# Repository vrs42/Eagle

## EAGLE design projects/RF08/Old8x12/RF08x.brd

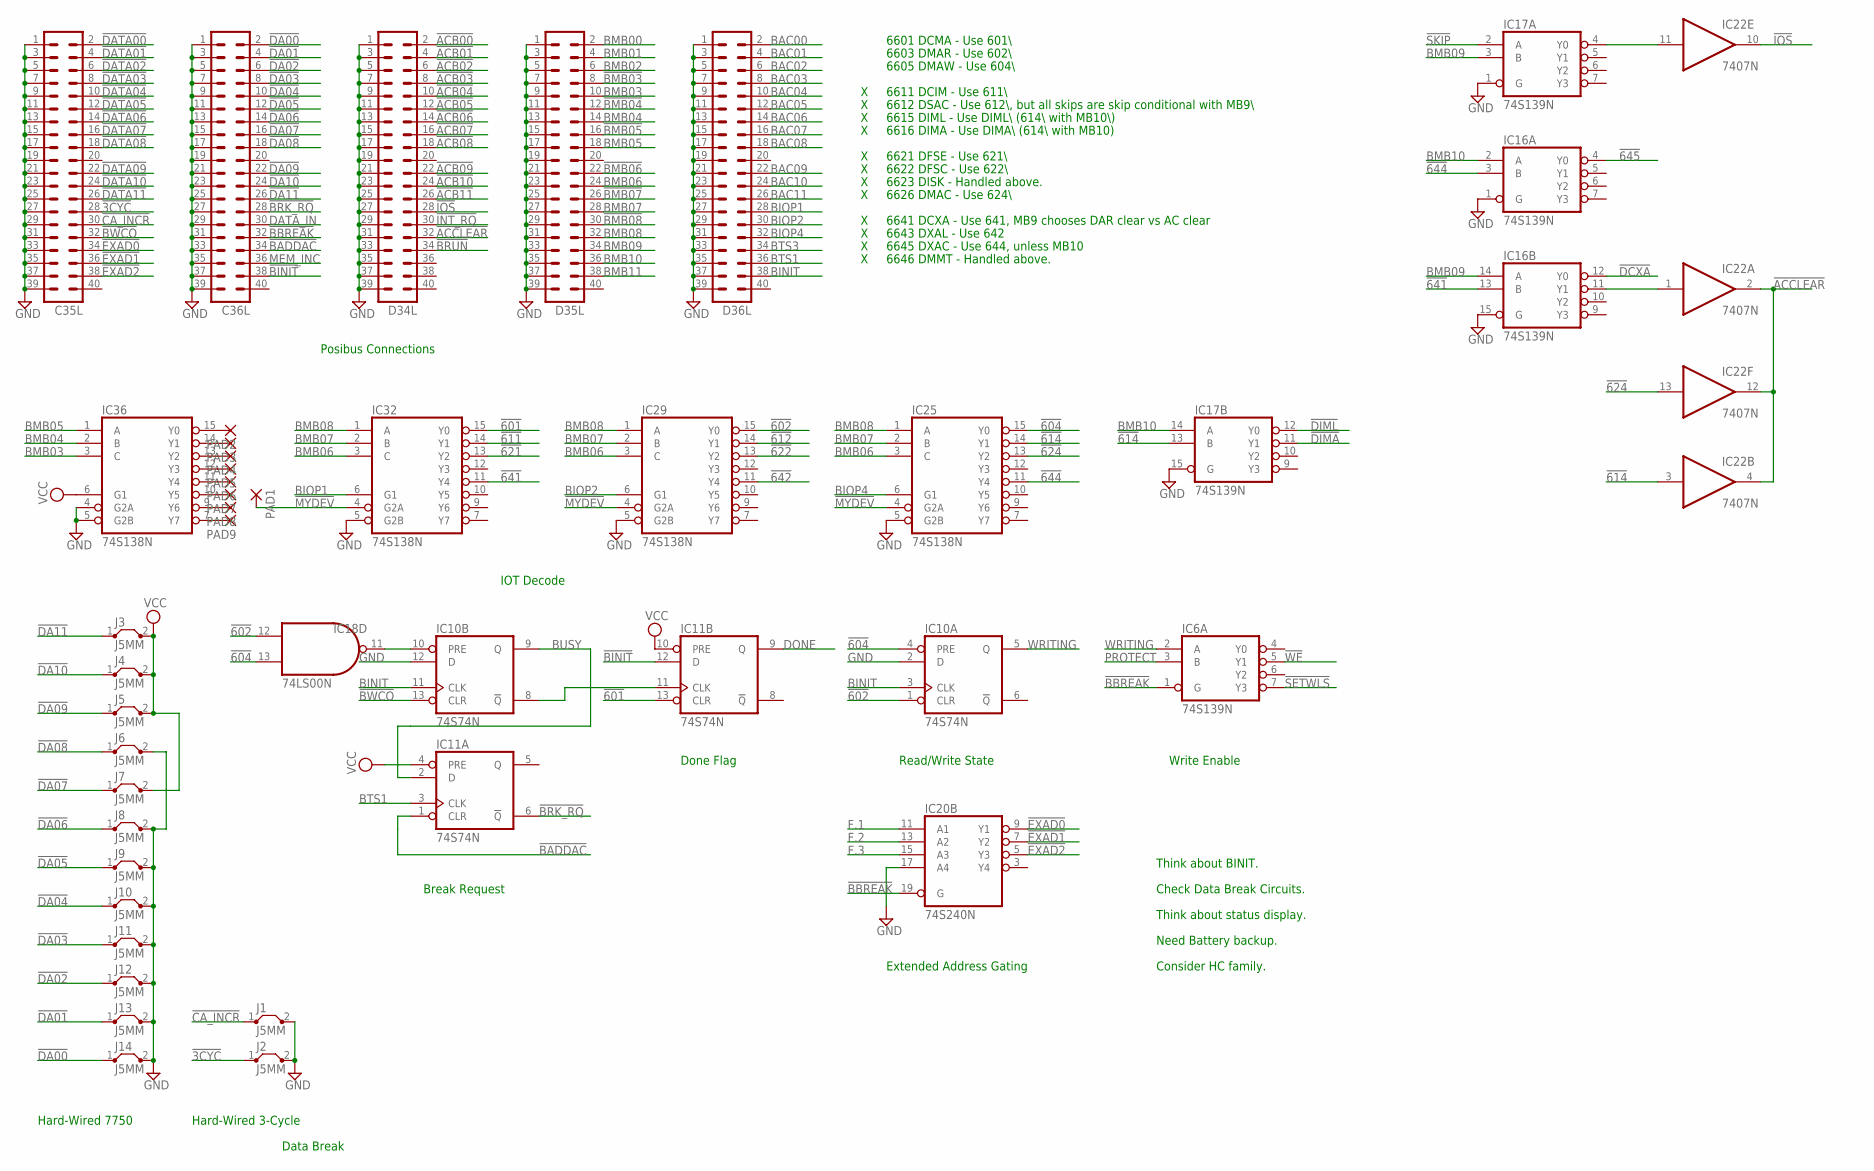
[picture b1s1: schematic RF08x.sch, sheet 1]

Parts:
C35L, C36L: MA20-2
D34L, D35L, D36L: MA20-2
IC6, IC16, IC17: 74S139N; DIL16
IC10, IC11: 74S74N; DIL14
IC18: 74LS00N; DIL14
IC20: 74S240N; DIL20
IC22: 7407N; DIL14
IC25, IC29, IC32, IC36: 74S138N; DIL16
J1, J2, J3, J4, J5, J6, J7, J8, J9, J10, J11, J12, J13, J14: J5MM; 05
PAD1, PAD2, PAD3, PAD4, PAD5, PAD6, PAD7, PAD8, PAD9: 1,6/0,8

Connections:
!3CYC: C35L.28, J2.1
!601: IC11.13 (CLR), IC32.15 (Y0); also elsewhere on the board
!602: IC10.1 (CLR), IC18.12 (I0), IC29.15 (Y0); also elsewhere on the board
!604: IC10.4 (PRE), IC18.13 (I1), IC25.15 (Y0); also elsewhere on the board
!611: IC32.14 (Y1); also elsewhere on the board
!612: IC29.14 (Y1); also elsewhere on the board
!614: IC17.13 (B), IC22.3 (I), IC25.14 (Y1)
!621: IC32.13 (Y2); also elsewhere on the board
!622: IC29.13 (Y2); also elsewhere on the board
!624: IC22.13 (I), IC25.13 (Y2); also elsewhere on the board
!641: IC16.13 (B), IC32.11 (Y4)
!642: IC29.11 (Y4); also elsewhere on the board
!644: IC16.3 (B), IC25.11 (Y4)
!645: IC16.4 (Y0); also elsewhere on the board
!ACB00: D34L.2; also elsewhere on the board
!ACB01: D34L.4; also elsewhere on the board
!ACB02: D34L.6; also elsewhere on the board
!ACB03: D34L.8; also elsewhere on the board
!ACB04: D34L.10; also elsewhere on the board
!ACB05: D34L.12; also elsewhere on the board
!ACB06: D34L.14; also elsewhere on the board
!ACB07: D34L.16; also elsewhere on the board
!ACB08: D34L.18; also elsewhere on the board
!ACB09: D34L.22; also elsewhere on the board
!ACB10: D34L.24; also elsewhere on the board
!ACB11: D34L.26; also elsewhere on the board
!ACCLEAR: D34L.32, IC22.2 (O), IC22.4 (O), IC22.12 (O)
!BADDAC: C36L.34, IC11.1 (CLR)
!BBREAK: C36L.32, IC6.1 (G), IC20.19 (G); also elsewhere on the board
!BINIT: C36L.38, IC11.12 (D)
!BMB03: D35L.8
!BMB04: D35L.12
!BMB05: D35L.16
!BMB06: D35L.22
!BMB07: D35L.26
!BMB08: D35L.30
!BRK_RQ: C36L.28, IC11.6 (!Q)
!BRUN: D34L.34
!BWCO: C35L.32, IC10.13 (CLR)
!CA_INCR: C35L.30, J1.1
!DA00: C36L.2, J14.1
!DA01: C36L.4, J13.1
!DA02: C36L.6, J12.1
!DA03: C36L.8, J11.1
!DA04: C36L.10, J10.1
!DA05: C36L.12, J9.1
!DA06: C36L.14, J8.1
!DA07: C36L.16, J7.1
!DA08: C36L.18, J6.1
!DA09: C36L.22, J5.1
!DA10: C36L.24, J4.1
!DA11: C36L.26, J3.1
!DATA00: C35L.2; also elsewhere on the board
!DATA01: C35L.4; also elsewhere on the board
!DATA02: C35L.6; also elsewhere on the board
!DATA03: C35L.8; also elsewhere on the board
!DATA04: C35L.10; also elsewhere on the board
!DATA05: C35L.12; also elsewhere on the board
!DATA06: C35L.14; also elsewhere on the board
!DATA07: C35L.16; also elsewhere on the board
!DATA08: C35L.18; also elsewhere on the board
!DATA09: C35L.22; also elsewhere on the board
!DATA10: C35L.24; also elsewhere on the board
!DATA11: C35L.26; also elsewhere on the board
!DCXA: IC16.12 (Y0); also elsewhere on the board
!DIMA: IC17.11 (Y1); also elsewhere on the board
!DIML: IC17.12 (Y0); also elsewhere on the board
!EXAD0: C35L.34, IC20.9 (Y1)
!EXAD1: C35L.36, IC20.7 (Y2)
!EXAD2: C35L.38, IC20.5 (Y3)
!INT_RQ: D34L.30; also elsewhere on the board
!IOS: D34L.28, IC22.10 (O)
!MYDEV: IC25.4 (G2A), IC29.4 (G2A), IC32.4 (G2A), PAD1.1
!SETWLS: IC6.7 (Y3); also elsewhere on the board
!SKIP: IC17.2 (A); also elsewhere on the board
!WE: IC6.5 (Y1); also elsewhere on the board
BAC00: D36L.2; also elsewhere on the board
BAC01: D36L.4; also elsewhere on the board
BAC02: D36L.6; also elsewhere on the board
BAC03: D36L.8; also elsewhere on the board
BAC04: D36L.10; also elsewhere on the board
BAC05: D36L.12; also elsewhere on the board
BAC06: D36L.14; also elsewhere on the board
BAC07: D36L.16; also elsewhere on the board
BAC08: D36L.18; also elsewhere on the board
BAC09: D36L.22; also elsewhere on the board
BAC10: D36L.24; also elsewhere on the board
BAC11: D36L.26; also elsewhere on the board
BINIT: D36L.38, IC10.3 (CLK), IC10.11 (CLK); also elsewhere on the board
BIOP1: D36L.28, IC32.6 (G1)
BIOP2: D36L.30, IC29.6 (G1)
BIOP4: D36L.32, IC25.6 (G1)
BMB00: D35L.2; also elsewhere on the board
BMB01: D35L.4; also elsewhere on the board
BMB02: D35L.6; also elsewhere on the board
BMB03: D35L.10, IC36.3 (C); also elsewhere on the board
BMB04: D35L.14, IC36.2 (B); also elsewhere on the board
BMB05: D35L.18, IC36.1 (A); also elsewhere on the board
BMB06: D35L.24, IC25.3 (C), IC29.3 (C), IC32.3 (C); also elsewhere on the board
BMB07: D35L.28, IC25.2 (B), IC29.2 (B), IC32.2 (B); also elsewhere on the board
BMB08: D35L.32, IC25.1 (A), IC29.1 (A), IC32.1 (A); also elsewhere on the board
BMB09: D35L.34, IC16.14 (A), IC17.3 (B); also elsewhere on the board
BMB10: D35L.36, IC16.2 (A), IC17.14 (A); also elsewhere on the board
BMB11: D35L.38; also elsewhere on the board
BTS1: D36L.36, IC11.3 (CLK)
BTS3: D36L.34
BUSY: IC10.9 (Q), IC11.2 (D); also elsewhere on the board
DATA_IN: C36L.30
DONE: IC11.9 (Q); also elsewhere on the board
F.1: IC20.11 (A1); also elsewhere on the board
F.2: IC20.13 (A2); also elsewhere on the board
F.3: IC20.15 (A3); also elsewhere on the board
GND: C35L.1, C35L.3, C35L.5, C35L.7, C35L.9, C35L.11, C35L.13, C35L.15, C35L.17, C35L.19, C35L.21, C35L.23, C35L.25, C35L.27, C35L.29, C35L.31, C35L.33, C35L.35, C35L.37, C35L.39, C36L.1, C36L.3, C36L.5, C36L.7, C36L.9, C36L.11, C36L.13, C36L.15, C36L.17, C36L.19, C36L.21, C36L.23, C36L.25, C36L.27, C36L.29, C36L.31, C36L.33, C36L.35, C36L.37, C36L.39, D34L.1, D34L.3, D34L.5, D34L.7, D34L.9, D34L.11, D34L.13, D34L.15, D34L.17, D34L.19, D34L.21, D34L.23, D34L.25, D34L.27, D34L.29, D34L.31, D34L.33, D34L.35, D34L.37, D34L.39, D35L.1, D35L.3, D35L.5, D35L.7, D35L.9, D35L.11, D35L.13, D35L.15, D35L.17, D35L.19, D35L.21, D35L.23, D35L.25, D35L.27, D35L.29, D35L.31, D35L.33, D35L.35, D35L.37, D35L.39, D36L.1, D36L.3, D36L.5, D36L.7, D36L.9, D36L.11, D36L.13, D36L.15, D36L.17, D36L.19, D36L.21, D36L.23, D36L.25, D36L.27, D36L.29, D36L.31, D36L.33, D36L.35, D36L.37, D36L.39, IC6.8 (GND), IC10.2 (D), IC10.7 (GND), IC10.12 (D), IC11.7 (GND), IC16.1 (G), IC16.8 (GND), IC16.15 (G), IC17.1 (G), IC17.8 (GND), IC17.15 (G), IC18.7 (GND), IC20.10 (GND), IC20.17 (A4), IC22.7 (GND), IC25.5 (G2B), IC25.8 (GND), IC29.5 (G2B), IC29.8 (GND), IC32.5 (G2B), IC32.8 (GND), IC36.4 (G2A), IC36.5 (G2B), IC36.8 (GND), J1.2, J2.2, J6.2, J8.2, J9.2, J10.2, J11.2, J12.2, J13.2, J14.2; also elsewhere on the board
MEM_INC: C36L.36
unnamed: IC36.9 (Y6), PAD8.1
unnamed: IC10.8 (!Q), IC11.11 (CLK)
unnamed: IC36.15 (Y0), PAD2.1
unnamed: IC36.14 (Y1), PAD3.1
unnamed: IC36.13 (Y2), PAD4.1
unnamed: IC36.12 (Y3), PAD5.1
unnamed: IC36.11 (Y4), PAD6.1
unnamed: IC36.10 (Y5), PAD7.1
unnamed: IC36.7 (Y7), PAD9.1
unnamed: IC16.11 (Y1), IC22.1 (I)
unnamed: IC17.4 (Y0), IC22.11 (I)
unnamed: IC10.10 (PRE), IC18.11 (O)
PROTECT: IC6.3 (B); also elsewhere on the board
VCC: IC6.16 (VCC), IC10.14 (VCC), IC11.4 (PRE), IC11.10 (PRE), IC11.14 (VCC), IC16.16 (VCC), IC17.16 (VCC), IC18.14 (VCC), IC20.20 (VCC), IC22.14 (VCC), IC25.16 (VCC), IC29.16 (VCC), IC32.16 (VCC), IC36.6 (G1), IC36.16 (VCC), J3.2, J4.2, J5.2, J7.2; also elsewhere on the board
WRITING: IC6.2 (A), IC10.5 (Q); also elsewhere on the board

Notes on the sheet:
6601 DCMA - Use 601\\
6603 DMAR - Use 602\\
6605 DMAW - Use 604\\
6611 DCIM - Use 611\\
6612 DSAC - Use 612\\, but all skips are skip conditional with MB9\\
6615 DIML - Use DIML\\ (614\\ with MB10\\)
6616 DIMA - Use DIMA\\ (614\\ with MB10)
6621 DFSE - Use 621\\
6622 DFSC - Use 622\\
6623 DISK - Handled above.
6626 DMAC - Use 624\\
6641 DCXA - Use 641, MB9 chooses DAR clear vs AC clear
6643 DXAL - Use 642
6645 DXAC - Use 644, unless MB10
6646 DMMT - Handled above.
Posibus Connections
IOT Decode
Data Break
Hard-Wired 7750
Hard-Wired 3-Cycle
Think about BINIT.
Think about status display.
Break Request
Need Battery backup.
Done Flag
Extended Address Gating
Read/Write State
Write Enable
Check Data Break Circuits.
Consider HC family.

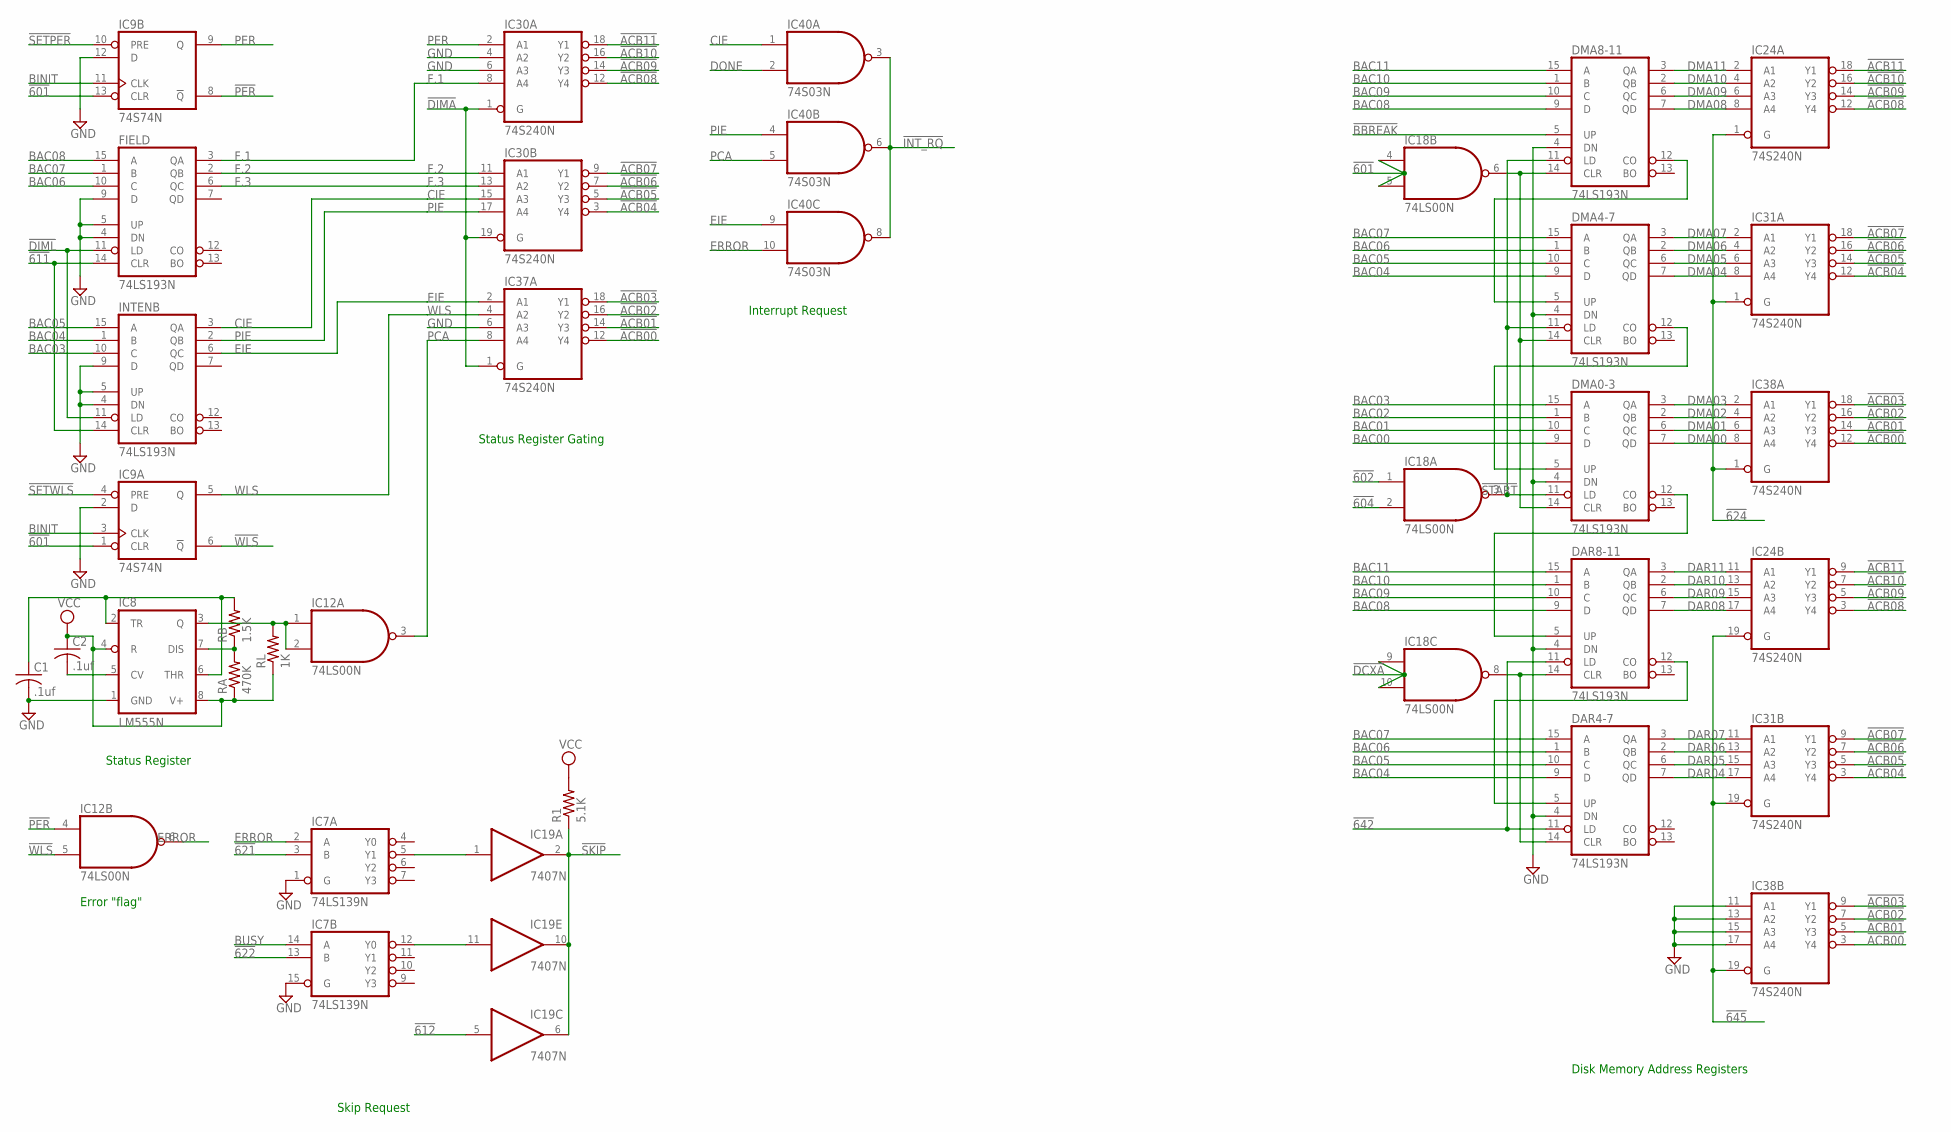
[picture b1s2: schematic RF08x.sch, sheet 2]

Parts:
C1, C2: .1uf; C050-025X075
DAR4-7, DAR8-11: 74LS193N; DIL16
DMA0-3, DMA4-7, DMA8-11: 74LS193N; DIL16
FIELD: 74LS193N; DIL16
IC7: 74LS139N; DIL16
IC8: LM555N; DIL08
IC9: 74S74N; DIL14
IC12, IC18: 74LS00N; DIL14
IC19: 7407N; DIL14
IC24, IC30, IC31, IC37, IC38: 74S240N; DIL20
IC40: 74S03N; DIL14
INTENB: 74LS193N; DIL16
R1: 5.1K; 0207/10
RA: 470K; 0207/10
RB: 1.5K; 0207/10
RL: 1K; 0207/10

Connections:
!601: IC9.1 (CLR), IC9.13 (CLR), IC18.4 (I0), IC18.5 (I1); also elsewhere on the board
!602: IC18.1 (I0); also elsewhere on the board
!604: IC18.2 (I1); also elsewhere on the board
!611: FIELD.14 (CLR), INTENB.14 (CLR); also elsewhere on the board
!612: IC19.5 (I); also elsewhere on the board
!621: IC7.3 (B); also elsewhere on the board
!622: IC7.13 (B); also elsewhere on the board
!624: IC24.1 (G), IC31.1 (G), IC38.1 (G); also elsewhere on the board
!642: DAR4-7.11 (LD), DAR8-11.11 (LD); also elsewhere on the board
!645: IC24.19 (G), IC31.19 (G), IC38.19 (G); also elsewhere on the board
!ACB00: IC37.12 (Y4), IC38.3 (Y4), IC38.12 (Y4); also elsewhere on the board
!ACB01: IC37.14 (Y3), IC38.5 (Y3), IC38.14 (Y3); also elsewhere on the board
!ACB02: IC37.16 (Y2), IC38.7 (Y2), IC38.16 (Y2); also elsewhere on the board
!ACB03: IC37.18 (Y1), IC38.9 (Y1), IC38.18 (Y1); also elsewhere on the board
!ACB04: IC30.3 (Y4), IC31.3 (Y4), IC31.12 (Y4); also elsewhere on the board
!ACB05: IC30.5 (Y3), IC31.5 (Y3), IC31.14 (Y3); also elsewhere on the board
!ACB06: IC30.7 (Y2), IC31.7 (Y2), IC31.16 (Y2); also elsewhere on the board
!ACB07: IC30.9 (Y1), IC31.9 (Y1), IC31.18 (Y1); also elsewhere on the board
!ACB08: IC24.3 (Y4), IC24.12 (Y4), IC30.12 (Y4); also elsewhere on the board
!ACB09: IC24.5 (Y3), IC24.14 (Y3), IC30.14 (Y3); also elsewhere on the board
!ACB10: IC24.7 (Y2), IC24.16 (Y2), IC30.16 (Y2); also elsewhere on the board
!ACB11: IC24.9 (Y1), IC24.18 (Y1), IC30.18 (Y1); also elsewhere on the board
!BBREAK: DMA8-11.5 (UP); also elsewhere on the board
!DCXA: IC18.9 (I0), IC18.10 (I1); also elsewhere on the board
!DIMA: IC30.1 (G), IC30.19 (G), IC37.1 (G); also elsewhere on the board
!DIML: FIELD.11 (LD), INTENB.11 (LD); also elsewhere on the board
!INT_RQ: IC40.3 (O), IC40.6 (O), IC40.8 (O); also elsewhere on the board
!PER: IC9.8 (!Q), IC12.4 (I0)
!SETPER: IC9.10 (PRE); also elsewhere on the board
!SETWLS: IC9.4 (PRE); also elsewhere on the board
!SKIP: IC19.2 (O), IC19.6 (O), IC19.10 (O), R1.1; also elsewhere on the board
!START: DMA0-3.11 (LD), DMA4-7.11 (LD), DMA8-11.11 (LD), IC18.3 (O)
!WLS: IC9.6 (!Q), IC12.5 (I1)
BAC00: DMA0-3.9 (D); also elsewhere on the board
BAC01: DMA0-3.10 (C); also elsewhere on the board
BAC02: DMA0-3.1 (B); also elsewhere on the board
BAC03: DMA0-3.15 (A), INTENB.10 (C); also elsewhere on the board
BAC04: DAR4-7.9 (D), DMA4-7.9 (D), INTENB.1 (B); also elsewhere on the board
BAC05: DAR4-7.10 (C), DMA4-7.10 (C), INTENB.15 (A); also elsewhere on the board
BAC06: DAR4-7.1 (B), DMA4-7.1 (B), FIELD.10 (C); also elsewhere on the board
BAC07: DAR4-7.15 (A), DMA4-7.15 (A), FIELD.1 (B); also elsewhere on the board
BAC08: DAR8-11.9 (D), DMA8-11.9 (D), FIELD.15 (A); also elsewhere on the board
BAC09: DAR8-11.10 (C), DMA8-11.10 (C); also elsewhere on the board
BAC10: DAR8-11.1 (B), DMA8-11.1 (B); also elsewhere on the board
BAC11: DAR8-11.15 (A), DMA8-11.15 (A); also elsewhere on the board
BINIT: IC9.3 (CLK), IC9.11 (CLK); also elsewhere on the board
BUSY: IC7.14 (A); also elsewhere on the board
CIE: IC30.15 (A3), IC40.1 (I0), INTENB.3 (QA)
DAR04: DAR4-7.7 (QD), IC31.17 (A4); also elsewhere on the board
DAR05: DAR4-7.6 (QC), IC31.15 (A3); also elsewhere on the board
DAR06: DAR4-7.2 (QB), IC31.13 (A2); also elsewhere on the board
DAR07: DAR4-7.3 (QA), IC31.11 (A1); also elsewhere on the board
DAR08: DAR8-11.7 (QD), IC24.17 (A4); also elsewhere on the board
DAR09: DAR8-11.6 (QC), IC24.15 (A3); also elsewhere on the board
DAR10: DAR8-11.2 (QB), IC24.13 (A2); also elsewhere on the board
DAR11: DAR8-11.3 (QA), IC24.11 (A1); also elsewhere on the board
DMA00: DMA0-3.7 (QD), IC38.8 (A4); also elsewhere on the board
DMA01: DMA0-3.6 (QC), IC38.6 (A3); also elsewhere on the board
DMA02: DMA0-3.2 (QB), IC38.4 (A2); also elsewhere on the board
DMA03: DMA0-3.3 (QA), IC38.2 (A1); also elsewhere on the board
DMA04: DMA4-7.7 (QD), IC31.8 (A4); also elsewhere on the board
DMA05: DMA4-7.6 (QC), IC31.6 (A3); also elsewhere on the board
DMA06: DMA4-7.2 (QB), IC31.4 (A2); also elsewhere on the board
DMA07: DMA4-7.3 (QA), IC31.2 (A1); also elsewhere on the board
DMA08: DMA8-11.7 (QD), IC24.8 (A4); also elsewhere on the board
DMA09: DMA8-11.6 (QC), IC24.6 (A3); also elsewhere on the board
DMA10: DMA8-11.2 (QB), IC24.4 (A2); also elsewhere on the board
DMA11: DMA8-11.3 (QA), IC24.2 (A1); also elsewhere on the board
DONE: IC40.2 (I1); also elsewhere on the board
EIE: IC37.2 (A1), IC40.9 (I0), INTENB.6 (QC)
ERROR: IC7.2 (A), IC12.6 (O), IC40.10 (I1)
F.1: FIELD.3 (QA), IC30.8 (A4); also elsewhere on the board
F.2: FIELD.2 (QB), IC30.11 (A1); also elsewhere on the board
F.3: FIELD.6 (QC), IC30.13 (A2); also elsewhere on the board
GND: C1.2, DAR4-7.4 (DN), DAR4-7.8 (GND), DAR8-11.4 (DN), DAR8-11.8 (GND), DMA0-3.4 (DN), DMA0-3.8 (GND), DMA4-7.4 (DN), DMA4-7.8 (GND), DMA8-11.4 (DN), DMA8-11.8 (GND), FIELD.4 (DN), FIELD.5 (UP), FIELD.8 (GND), FIELD.9 (D), IC7.1 (G), IC7.8 (GND), IC7.15 (G), IC8.1 (GND), IC9.2 (D), IC9.7 (GND), IC9.12 (D), IC12.7 (GND), IC18.7 (GND), IC19.7 (GND), IC24.10 (GND), IC30.4 (A2), IC30.6 (A3), IC30.10 (GND), IC31.10 (GND), IC37.6 (A3), IC37.10 (GND), IC38.10 (GND), IC38.11 (A1), IC38.13 (A2), IC38.15 (A3), IC38.17 (A4), IC40.7 (GND), INTENB.4 (DN), INTENB.5 (UP), INTENB.8 (GND), INTENB.9 (D); also elsewhere on the board
unnamed: DMA0-3.5 (UP), DMA4-7.12 (CO)
unnamed: DAR4-7.14 (CLR), DAR8-11.14 (CLR), IC18.8 (O)
unnamed: DMA4-7.5 (UP), DMA8-11.12 (CO)
unnamed: DAR8-11.5 (UP), DMA0-3.12 (CO)
unnamed: DMA0-3.14 (CLR), DMA4-7.14 (CLR), DMA8-11.14 (CLR), IC18.6 (O)
unnamed: DAR4-7.5 (UP), DAR8-11.12 (CO)
unnamed: IC7.5 (Y1), IC19.1 (I)
unnamed: IC8.7 (DIS), RA.2, RB.1
unnamed: IC8.3 (Q), IC12.1 (I0), IC12.2 (I1), RL.2
unnamed: C1.1, IC8.2 (TR), IC8.6 (THR), RB.2
unnamed: IC7.12 (Y0), IC19.11 (I)
unnamed: C2.2, IC8.5 (CV)
PCA: IC12.3 (O), IC37.8 (A4), IC40.5 (I1)
PER: IC9.9 (Q), IC30.2 (A1)
PIE: IC30.17 (A4), IC40.4 (I0), INTENB.2 (QB)
VCC: C2.1, DAR4-7.16 (VCC), DAR8-11.16 (VCC), DMA0-3.16 (VCC), DMA4-7.16 (VCC), DMA8-11.16 (VCC), FIELD.16 (VCC), IC7.16 (VCC), IC8.4 (R), IC8.8 (V+), IC9.14 (VCC), IC12.14 (VCC), IC18.14 (VCC), IC19.14 (VCC), IC24.20 (VCC), IC30.20 (VCC), IC31.20 (VCC), IC37.20 (VCC), IC38.20 (VCC), IC40.14 (VCC), INTENB.16 (VCC), R1.2, RA.1, RL.1; also elsewhere on the board
WLS: IC9.5 (Q), IC37.4 (A2)

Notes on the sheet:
Disk Memory Address Registers
Status Register
Status Register Gating
Interrupt Request
Error "flag"
Skip Request

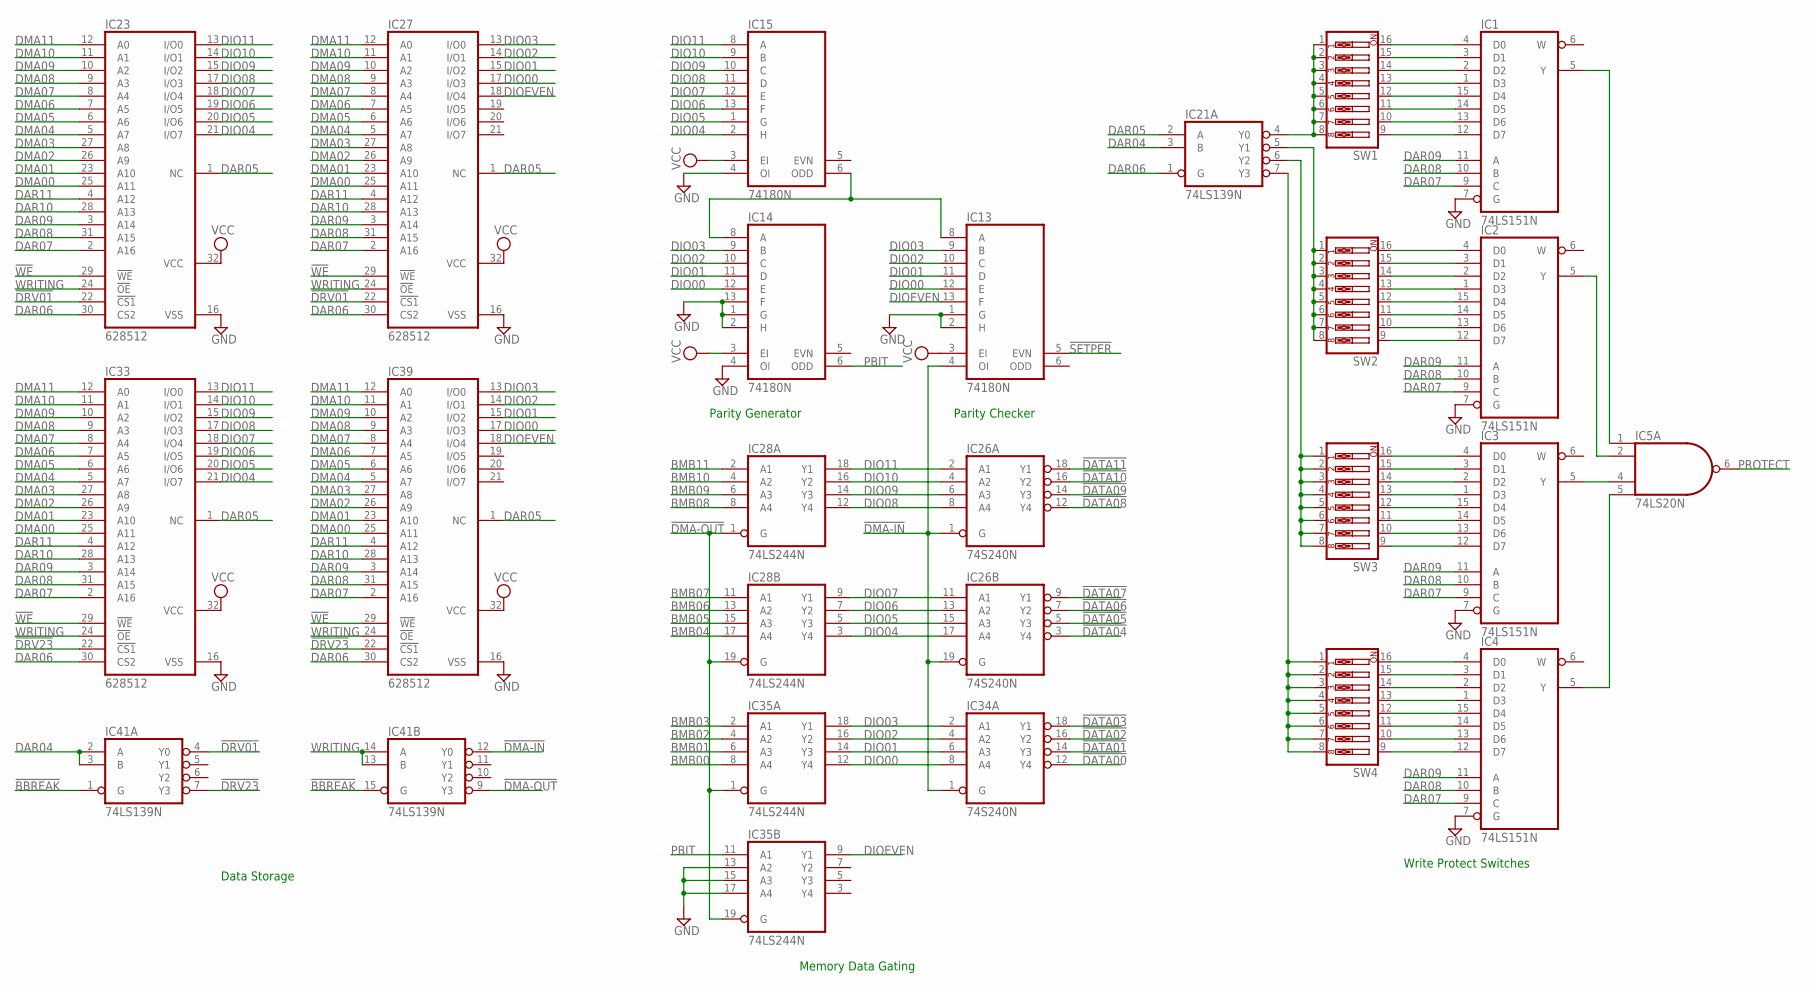
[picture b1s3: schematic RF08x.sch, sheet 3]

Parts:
IC1, IC2, IC3, IC4: 74LS151N; DIL16
IC5: 74LS20N; DIL14
IC13, IC14, IC15: 74180N; DIL14
IC21, IC41: 74LS139N; DIL16
IC23, IC27, IC33, IC39: 628512; DIL32
IC26, IC34: 74S240N; DIL20
IC28, IC35: 74LS244N; DIL20
SW1, SW2, SW3, SW4: SW_DIP-8; EDG-08

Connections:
!BBREAK: IC41.1 (G), IC41.15 (G); also elsewhere on the board
!DATA00: IC34.12 (Y4); also elsewhere on the board
!DATA01: IC34.14 (Y3); also elsewhere on the board
!DATA02: IC34.16 (Y2); also elsewhere on the board
!DATA03: IC34.18 (Y1); also elsewhere on the board
!DATA04: IC26.3 (Y4); also elsewhere on the board
!DATA05: IC26.5 (Y3); also elsewhere on the board
!DATA06: IC26.7 (Y2); also elsewhere on the board
!DATA07: IC26.9 (Y1); also elsewhere on the board
!DATA08: IC26.12 (Y4); also elsewhere on the board
!DATA09: IC26.14 (Y3); also elsewhere on the board
!DATA10: IC26.16 (Y2); also elsewhere on the board
!DATA11: IC26.18 (Y1); also elsewhere on the board
!DMA-IN: IC13.4 (OI), IC26.1 (G), IC26.19 (G), IC34.1 (G), IC41.12 (Y0)
!DMA-OUT: IC28.1 (G), IC28.19 (G), IC35.1 (G), IC35.19 (G), IC41.9 (Y3)
!DRV01: IC23.22 (!CS1), IC27.22 (!CS1), IC41.4 (Y0)
!DRV23: IC33.22 (!CS1), IC39.22 (!CS1), IC41.7 (Y3)
!SETPER: IC13.5 (EVN); also elsewhere on the board
!WE: IC23.29 (!WE), IC27.29 (!WE), IC33.29 (!WE), IC39.29 (!WE); also elsewhere on the board
BMB00: IC35.8 (A4); also elsewhere on the board
BMB01: IC35.6 (A3); also elsewhere on the board
BMB02: IC35.4 (A2); also elsewhere on the board
BMB03: IC35.2 (A1); also elsewhere on the board
BMB04: IC28.17 (A4); also elsewhere on the board
BMB05: IC28.15 (A3); also elsewhere on the board
BMB06: IC28.13 (A2); also elsewhere on the board
BMB07: IC28.11 (A1); also elsewhere on the board
BMB08: IC28.8 (A4); also elsewhere on the board
BMB09: IC28.6 (A3); also elsewhere on the board
BMB10: IC28.4 (A2); also elsewhere on the board
BMB11: IC28.2 (A1); also elsewhere on the board
DAR04: IC21.3 (B), IC41.2 (A), IC41.3 (B); also elsewhere on the board
DAR05: IC21.2 (A), IC23.1 (NC), IC27.1 (NC), IC33.1 (NC), IC39.1 (NC); also elsewhere on the board
DAR06: IC21.1 (G), IC23.30 (CS2), IC27.30 (CS2), IC33.30 (CS2), IC39.30 (CS2); also elsewhere on the board
DAR07: IC1.9 (C), IC2.9 (C), IC3.9 (C), IC4.9 (C), IC23.2 (A16), IC27.2 (A16), IC33.2 (A16), IC39.2 (A16); also elsewhere on the board
DAR08: IC1.10 (B), IC2.10 (B), IC3.10 (B), IC4.10 (B), IC23.31 (A15), IC27.31 (A15), IC33.31 (A15), IC39.31 (A15); also elsewhere on the board
DAR09: IC1.11 (A), IC2.11 (A), IC3.11 (A), IC4.11 (A), IC23.3 (A14), IC27.3 (A14), IC33.3 (A14), IC39.3 (A14); also elsewhere on the board
DAR10: IC23.28 (A13), IC27.28 (A13), IC33.28 (A13), IC39.28 (A13); also elsewhere on the board
DAR11: IC23.4 (A12), IC27.4 (A12), IC33.4 (A12), IC39.4 (A12); also elsewhere on the board
DIO00: IC13.12 (E), IC14.12 (E), IC27.17 (I/O3), IC34.8 (A4), IC35.12 (Y4), IC39.17 (I/O3)
DIO01: IC13.11 (D), IC14.11 (D), IC27.15 (I/O2), IC34.6 (A3), IC35.14 (Y3), IC39.15 (I/O2)
DIO02: IC13.10 (C), IC14.10 (C), IC27.14 (I/O1), IC34.4 (A2), IC35.16 (Y2), IC39.14 (I/O1)
DIO03: IC13.9 (B), IC14.9 (B), IC27.13 (I/O0), IC34.2 (A1), IC35.18 (Y1), IC39.13 (I/O0)
DIO04: IC15.2 (H), IC23.21 (I/O7), IC26.17 (A4), IC28.3 (Y4), IC33.21 (I/O7)
DIO05: IC15.1 (G), IC23.20 (I/O6), IC26.15 (A3), IC28.5 (Y3), IC33.20 (I/O6)
DIO06: IC15.13 (F), IC23.19 (I/O5), IC26.13 (A2), IC28.7 (Y2), IC33.19 (I/O5)
DIO07: IC15.12 (E), IC23.18 (I/O4), IC26.11 (A1), IC28.9 (Y1), IC33.18 (I/O4)
DIO08: IC15.11 (D), IC23.17 (I/O3), IC26.8 (A4), IC28.12 (Y4), IC33.17 (I/O3)
DIO09: IC15.10 (C), IC23.15 (I/O2), IC26.6 (A3), IC28.14 (Y3), IC33.15 (I/O2)
DIO10: IC15.9 (B), IC23.14 (I/O1), IC26.4 (A2), IC28.16 (Y2), IC33.14 (I/O1)
DIO11: IC15.8 (A), IC23.13 (I/O0), IC26.2 (A1), IC28.18 (Y1), IC33.13 (I/O0)
DIOEVEN: IC13.13 (F), IC27.18 (I/O4), IC35.9 (Y1), IC39.18 (I/O4)
DMA00: IC23.25 (A11), IC27.25 (A11), IC33.25 (A11), IC39.25 (A11); also elsewhere on the board
DMA01: IC23.23 (A10), IC27.23 (A10), IC33.23 (A10), IC39.23 (A10); also elsewhere on the board
DMA02: IC23.26 (A9), IC27.26 (A9), IC33.26 (A9), IC39.26 (A9); also elsewhere on the board
DMA03: IC23.27 (A8), IC27.27 (A8), IC33.27 (A8), IC39.27 (A8); also elsewhere on the board
DMA04: IC23.5 (A7), IC27.5 (A7), IC33.5 (A7), IC39.5 (A7); also elsewhere on the board
DMA05: IC23.6 (A6), IC27.6 (A6), IC33.6 (A6), IC39.6 (A6); also elsewhere on the board
DMA06: IC23.7 (A5), IC27.7 (A5), IC33.7 (A5), IC39.7 (A5); also elsewhere on the board
DMA07: IC23.8 (A4), IC27.8 (A4), IC33.8 (A4), IC39.8 (A4); also elsewhere on the board
DMA08: IC23.9 (A3), IC27.9 (A3), IC33.9 (A3), IC39.9 (A3); also elsewhere on the board
DMA09: IC23.10 (A2), IC27.10 (A2), IC33.10 (A2), IC39.10 (A2); also elsewhere on the board
DMA10: IC23.11 (A1), IC27.11 (A1), IC33.11 (A1), IC39.11 (A1); also elsewhere on the board
DMA11: IC23.12 (A0), IC27.12 (A0), IC33.12 (A0), IC39.12 (A0); also elsewhere on the board
GND: IC1.7 (G), IC1.8 (GND), IC2.7 (G), IC2.8 (GND), IC3.7 (G), IC3.8 (GND), IC4.7 (G), IC4.8 (GND), IC5.7 (GND), IC13.1 (G), IC13.2 (H), IC13.7 (GND), IC14.1 (G), IC14.2 (H), IC14.4 (OI), IC14.7 (GND), IC14.13 (F), IC15.4 (OI), IC15.7 (GND), IC21.8 (GND), IC23.16 (VSS), IC26.10 (GND), IC27.16 (VSS), IC28.10 (GND), IC33.16 (VSS), IC34.10 (GND), IC35.10 (GND), IC35.13 (A2), IC35.15 (A3), IC35.17 (A4), IC39.16 (VSS), IC41.8 (GND); also elsewhere on the board
unnamed: IC21.4 (Y0), SW1.1, SW1.2, SW1.3, SW1.4, SW1.5, SW1.6, SW1.7, SW1.8
unnamed: IC13.8 (A), IC14.8 (A), IC15.6 (ODD)
unnamed: IC2.5 (Y), IC5.2 (I1)
unnamed: IC21.5 (Y1), SW2.1, SW2.2, SW2.3, SW2.4, SW2.5, SW2.6, SW2.7, SW2.8
unnamed: IC21.6 (Y2), SW3.1, SW3.2, SW3.3, SW3.4, SW3.5, SW3.6, SW3.7, SW3.8
unnamed: IC21.7 (Y3), SW4.1, SW4.2, SW4.3, SW4.4, SW4.5, SW4.6, SW4.7, SW4.8
unnamed: IC3.5 (Y), IC5.4 (I2)
unnamed: IC1.5 (Y), IC5.1 (I0)
unnamed: IC4.5 (Y), IC5.5 (I3)
unnamed: IC1.4 (D0), SW1.16
unnamed: IC1.3 (D1), SW1.15
unnamed: IC1.2 (D2), SW1.14
unnamed: IC1.1 (D3), SW1.13
unnamed: IC1.14 (D5), SW1.11
unnamed: IC1.13 (D6), SW1.10
unnamed: IC1.12 (D7), SW1.9
unnamed: IC1.15 (D4), SW1.12
unnamed: IC2.4 (D0), SW2.16
unnamed: IC2.3 (D1), SW2.15
unnamed: IC2.2 (D2), SW2.14
unnamed: IC2.1 (D3), SW2.13
unnamed: IC2.14 (D5), SW2.11
unnamed: IC2.13 (D6), SW2.10
unnamed: IC2.12 (D7), SW2.9
unnamed: IC3.4 (D0), SW3.16
unnamed: IC3.3 (D1), SW3.15
unnamed: IC3.2 (D2), SW3.14
unnamed: IC3.1 (D3), SW3.13
unnamed: IC3.14 (D5), SW3.11
unnamed: IC3.13 (D6), SW3.10
unnamed: IC3.12 (D7), SW3.9
unnamed: IC4.4 (D0), SW4.16
unnamed: IC4.3 (D1), SW4.15
unnamed: IC4.2 (D2), SW4.14
unnamed: IC4.1 (D3), SW4.13
unnamed: IC4.14 (D5), SW4.11
unnamed: IC4.13 (D6), SW4.10
unnamed: IC4.12 (D7), SW4.9
unnamed: IC4.15 (D4), SW4.12
unnamed: IC3.15 (D4), SW3.12
unnamed: IC2.15 (D4), SW2.12
PBIT: IC14.6 (ODD), IC35.11 (A1)
PROTECT: IC5.6 (O); also elsewhere on the board
VCC: IC1.16 (VCC), IC2.16 (VCC), IC3.16 (VCC), IC4.16 (VCC), IC5.14 (VCC), IC13.3 (EI), IC13.14 (VCC), IC14.3 (EI), IC14.14 (VCC), IC15.3 (EI), IC15.14 (VCC), IC21.16 (VCC), IC23.32 (VCC), IC26.20 (VCC), IC27.32 (VCC), IC28.20 (VCC), IC33.32 (VCC), IC34.20 (VCC), IC35.20 (VCC), IC39.32 (VCC), IC41.16 (VCC); also elsewhere on the board
WRITING: IC23.24 (!OE), IC27.24 (!OE), IC33.24 (!OE), IC39.24 (!OE), IC41.13 (B), IC41.14 (A); also elsewhere on the board

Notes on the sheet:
Parity Generator
Parity Checker
Memory Data Gating
Write Protect Switches
Data Storage

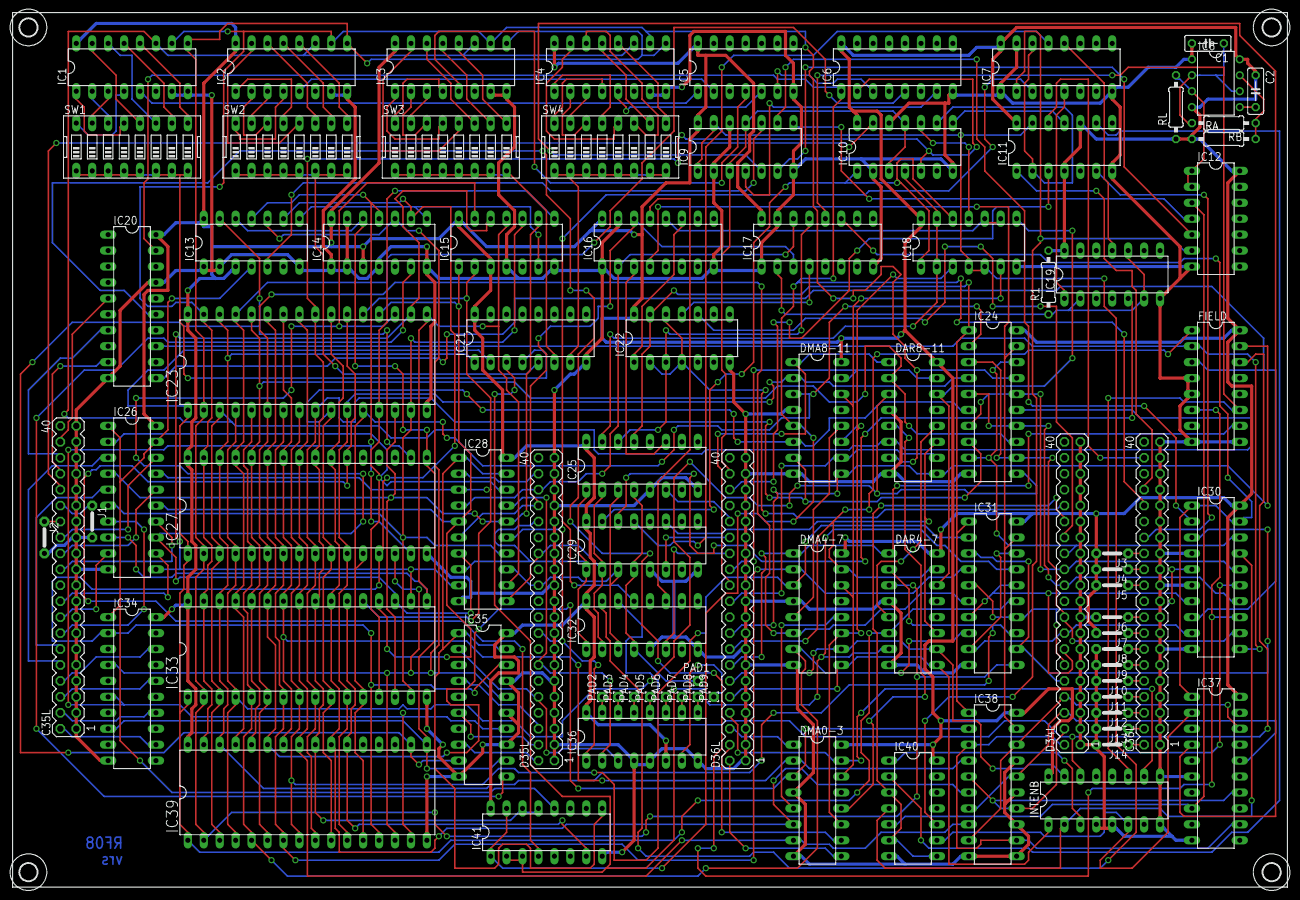
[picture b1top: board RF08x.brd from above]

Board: 2 copper layers, 203.2 x 139.4 mm, 90 parts (0 on the bottom side), 221 nets.

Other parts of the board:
U$1, U$2, U$3, U$4: 2,8

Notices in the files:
projects/RF08/Old8x12/RS08-.brd:
DF32x4 Disk Emulator Rev. B (c)2003 CEMorris
